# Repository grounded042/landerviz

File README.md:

# LanderViz

LanderViz is a stand-alone audio visualizer for a ZSA Moonlander Mark I. A
SparkFun Pro Micro RP2040 sits between the keyboard and the Mac, analyzes a
stereo audio pair, and targets 30 frames per second of per-key color to custom
Moonlander firmware. No visualizer program runs on the Mac during stand-alone
operation; the optional Mac preview exists only for development.

The complete stereo prototype has been hardware validated: both audio channels
drive the display and keyboard independently, the Moonlander receives RGB
frames, and ordinary typing passes through to macOS. The Moonlander output is
specifically for **revision A**.

## Architecture

```text
                             ordinary keyboard/mouse/media reports
Moonlander -- downstream USB --> Pro Micro RP2040 -- upstream USB --> hub --> Mac
     ^                           |  host toward keyboard; device toward Mac
     |                           +-- stereo ADC + FFT
     +---------- RGB frames -----+-- LCD + rotary encoder
```

- **HID** (Human Interface Device) is the standard USB keyboard/mouse protocol.
  TinyUSB makes LanderViz appear as a composite keyboard, mouse, media-key, and
  system-control device to the Mac and forwards the Moonlander's reports.
- **PIO** (Programmable Input/Output) is configurable digital hardware inside
  the RP2040. Pico-PIO-USB uses it to create the second USB connection on GPIO0
  and GPIO1, where LanderViz acts as the host for the real Moonlander.
- **Raw HID** is a vendor-defined HID data pipe. LanderViz owns that pipe and
  sends each RGB frame as eight 32-byte packets. The Moonlander publishes only
  complete frames, so a dropped packet cannot make a torn frame.
- **ADC** (analog-to-digital converter) samples biased left and right audio on
  GPIO26 and GPIO27. The RP2040 uses ARM CMSIS-DSP's 256-point Q15 **FFT**
  (fast Fourier transform) to split audio into frequency bands. FLOW averages
  left and right before one FFT; SPECTRUM retains one FFT per channel. Q15 is a
  signed fixed-point number format with 15 fractional bits.

The custom firmware deliberately removes ZSA's Oryx Raw HID module. Normal
typing, layers, macros, mouse keys, media keys, and N-key rollover remain; the
live Keymapp layout display and Oryx Live Training do not. Keymapp is not
required for normal use and remains optional as a firmware flashing tool.

If RGB packets stop for 500 ms, the keyboard returns to the layer lighting from
your Oryx layout. Both firmwares cap LED brightness at 175/255.

## Reproducible Nix builds

The flake pins the Raspberry Pi Pico software development kit, TinyUSB,
Pico-PIO-USB, ARM CMSIS-DSP, ZSA QMK Firmware 25, and QMK's required
submodules.
The generated Oryx keymap source is vendored as reviewable text under
`moonlander/oryx`; its source and refresh procedure are documented in
`moonlander/README.md`.

```sh
nix flake check
nix build .#rp2040 -o result-rp2040
nix build .#moonlander -o result-moonlander
nix build .#preview -o result-preview
nix build .#power-capture -o result-power-capture
nix build .#rp2040-power-test -o result-rp2040-power-test
nix build .#rp2040-encoder-test -o result-rp2040-encoder-test
nix build .#moonlander-power-test -o result-moonlander-power-test
```

Artifacts:

- `result-rp2040/landerviz.uf2` — Pro Micro RP2040 firmware
- `result-moonlander/zsa_moonlander_reva_landerviz.bin` — Moonlander revision-A
  firmware based on Oryx layout `z9wlG`, revision `ARDpK`
- `result-preview/bin/landerviz-preview` — development-only Mac visualizer
- `result-power-capture/bin/landerviz-power-capture` — FNIRSI FNB58 power
  measurement logger
- `result-rp2040-power-test/landerviz.uf2` — manual all-white power-test
  controller firmware
- `result-rp2040-encoder-test/landerviz.uf2` — rotary encoder wiring and
  transition diagnostic
- `result-moonlander-power-test/zsa_moonlander_reva_landerviz.bin` — matching
  Moonlander revision-A diagnostic firmware with its receive cap raised to 255

`nix develop` provides the pinned build tools for manual CMake work. The actual
build board name is `sparkfun_promicro`; the flake already supplies it.

### USB power capture

The development-only power logger reads an FNIRSI FNB58 through its separate
micro-USB `PC` port while the meter remains inline between the powered hub and
LanderViz. **HID** (Human Interface Device) is used here only as the meter's
driver-free USB data transport. The tool reports the lowest measured USB bus
voltage and the average and highest current and power. It can also retain every
sample as a **CSV** (comma-separated values) file for later inspection.

```sh
nix run .#power-capture -- --duration 30
nix run .#power-capture -- --duration 30 --csv /tmp/landerviz-power.csv
```

Leave the FNB58 `PD` communication switch off. The logger implements only the
meter's initialization and measurement-poll commands; it has no fast-charge or
voltage-trigger feature. Its USB measurement protocol is based on the
independently documented [OpenFNB58 protocol](https://github.com/yeckel/OpenFNB58).

#### Controlled maximum-light test

The power-test artifacts are measurement tools, not production firmware. Flash
the diagnostic Moonlander image first, then the diagnostic RP2040 image. The
keyboard starts black after the USB bridge connects. A short press on the
encoder knob advances all keys through white levels 0, 64, 128, 175,
200, 225, and 255; a press held longer than 800 milliseconds moves down one
level. The LCD always shows the commanded level. A controller reset returns to
black.

Run the FNB58 logger during the test and advance only after checking the prior
plateau. Stop if USB disconnects, the keyboard resets or flickers, or its supply
voltage becomes marginal. Restore the ordinary `moonlander` and `rp2040`
artifacts after measurement; they retain the production cap of 175.

The 2026-10-22 breadboard test validated 175 as the production limit. With the
revision-A serial LCD configuration, a five-minute all-white soak at 175
averaged 0.713 A and peaked at 0.724 A; the lowest upstream VBUS reading was
5.174 V. White at 200 had previously shifted red/orange and recovered only
after reducing the test level to 64; 225 and 255 also failed. This is evidence
of a sustained-load limit somewhere in the prototype's downstream power path
even though voltage at the upstream FNB58 remained stable. Do not raise
`BRIGHTNESS_CAP` above 175 on the breadboard. [PCB.md](PCB.md) records the
complete measurement baseline and the remaining USB-C power decision.

### Mac visualization preview

The development-only preview uses the same C++ audio analyzer, FLOW v3
components, and Moonlander LED mapping as the RP2040 firmware. It defaults to
the accepted FLOW v3 compositor; press `T` to cycle through v1, the frozen v2
baseline, and v3 at the same playback position. The comparison engines and
isolated labs remain preview-only.
See [FLOW v3 design contract](FLOW_V3_DESIGN.md) for the model and acceptance
criteria. FFmpeg decodes MP3, M4A, WAV, FLAC, and other common audio files;
SDL2 provides playback and draws all 72 simulated keys. Neither dependency is
included in the firmware.

```sh
nix run .#preview -- ~/Music/test-track.mp3
nix run .#preview -- --demo
nix run .#preview -- --demo-kicks
nix run .#preview -- --fps 25 ~/Music/test-track.mp3
nix run .#preview -- --travel-ms 110 ~/Music/test-track.mp3
nix run .#preview -- --trace /tmp/flow.csv ~/Music/test-track.mp3
nix run .#preview -- --analyze-only --trace /tmp/flow.csv ~/Music/test-track.mp3
```

The macOS package also includes a real application bundle. Opening it with no
arguments starts the demo; use `--args` to play a local audio file:

```sh
open -n result-preview/LanderViz.app
open -n result-preview/LanderViz.app --args --fps 30 "/absolute/path/song.mp3"
```

Use `T` to cycle FLOW v1/v2/v3 at the same playback position, left/right or
number keys 1–5 to change mode, space to pause, `R` to restart, `G` to compare
realistic light spill with the flat diagnostic view, `M` to cycle the v3
Combined/Energy/Attack/Texture/Mid/Bass views, `B` to compare Bass A/B inside
the Bass Lab, `E` to compare Combined with/without its capped Energy floor, `A` to
compare Combined with/without its accepted Attack shaping, `X` to compare
Combined with/without its bounded Texture hue influence, `[`/`]` to change the
simulated frame rate, comma/period to make FLOW
slower/faster in 10 ms increments, and escape or `Q` to quit. The title bar
shows the active FLOW engine, mode, frame rate, FLOW travel time, and lighting
style.
`--travel-ms N` sets the initial 50–1000 ms per-column travel time. `--frames
N` exits after N rendered frames and is intended for automated smoke tests.
`--flow-v1`, `--flow-v2`, or `--flow-v3` selects an engine at startup. The
default is v3. Within v3, `M` cycles the Combined, isolated Energy, isolated
Attack, isolated Texture, isolated Mid, and frozen Bass views;
`--combined-lab`, `--energy-lab`, `--attack-lab`, `--texture-lab`, `--mid-lab`,
and `--bass-lab` choose the startup view, with Combined as the default. In the
Bass Lab, `B` switches between the frozen direct bass envelope (Lab A) and
bounded slow-bed contrast expansion (Lab B); `--bass-a` and `--bass-b` choose
the bass version, with the accepted Lab B bass foundation as the default.
Combined always uses Bass B. Its Energy floor is enabled by default;
`--energy-floor` and `--no-energy-floor` select it at startup.
Combined's Attack shaping is also enabled by default; `--attack-shape` and
`--no-attack-shape` select it at startup. Attack shaping requires the Energy
floor integration, so disabling the floor displays the earlier no-floor
Combined baseline. Texture integration is enabled by default;
`--texture-surface` and `--no-texture-surface` select it at startup. It is
layered on the accepted Energy and Attack integration, so disabling either
shows that earlier baseline. `--trace
FILE.csv` records the pre-gain gate,
shared gain, per-channel energy, centroid, dominance, and low/mid/high onset
flux, adaptive thresholds, strengths, and trigger decisions once per analyzed
audio frame, plus the v3 bass and midrange level, absolute and contrast
centroids, contrast strength, base/target/rendered hue, and presence
diagnostics, the isolated Energy Lab raw, target, and smoothed levels, and
Attack Lab's raw and normalized positive-rise signals. Texture Lab adds its raw
high-frequency share, target, smoothed texture, and presence. Add
`--analyze-only` to process the complete track without opening a window or
playing audio; it requires `--trace` and an audio file and prints the three
accepted v2 onset counts when complete. FLOW v2 keeps its base color and
energy stereo, but merges per-band energy across channels for shared rhythmic
events so a panned hit launches one wavefront across both keyboard halves.
`--demo-kicks` plays an isolated 120 BPM kick train and reports detected versus
generated v1 kicks in the title bar. V1 kick packets are enabled only in that
diagnostic mode while the detector is being calibrated. V3 Attack Lab is a
separate continuous positive-rise diagnostic with no threshold, refractory
timer, or binary beat trigger. Accepted Combined uses that signal only to
tighten an existing ribbon edge; it cannot independently create light.

Before flashing a Moonlander build, confirm the keyboard's hardware revision.
ZSA's command-line flasher can accept the local file:

```sh
nix run github:zsa/zapp -- flash result-moonlander/zsa_moonlander_reva_landerviz.bin
```

That command intentionally is not run by the build. Hold BOOT while connecting
the Pro Micro, then copy `landerviz.uf2` to the `RPI-RP2` drive to flash it.

## Minimal prototype parts

In addition to the parts already listed, the USB bridge needs:

- one USB-A female breakout, or a known-good female extension cable cut open;
- two 22 ohm resistors, one in each USB data wire;
- one bulk electrolytic capacitor, start with 470 microfarads rated for at
  least 6.3 V;
- a way to make reliable connections to the headerless boards: normally two
  12-pin 0.1-inch male headers for the Pro Micro, soldered in place;
- one 3.5 mm TRS stereo jack breakout and a male-to-male TRS cable, four
  100 kilohm resistors, and two 10 microfarad coupling capacitors;
- one 5 V, HD44780-compatible 16x2 LCD with a soldered PCF8574T I2C backpack;
  and
- one four-channel, bidirectional 3.3 V-to-5 V logic-level converter.

No larger controller or extra interface board is required. Keep the USB data
wires short; a solderless breadboard may be electrically marginal at USB full
speed, so first failures there do not automatically imply a firmware bug.

## Wiring

### USB bridge

The Pro Micro's onboard USB-C connector is the upstream/device connection to a
**data port** on the powered Anker hub. Never use a PowerIQ charging-only port.
The added USB-A female connector is the downstream/host connection for the
Moonlander. Use a known-good data cable: a charging-only USB cable can power the
Moonlander's startup LEDs while leaving LanderViz at `WAIT` indefinitely.

| USB-A female contact | Pro Micro connection |
|---|---|
| VBUS | backside `V` USB-power pad |
| D- | GPIO1 through 22 ohms |
| D+ | GPIO0 through 22 ohms |
| GND | GND |

**VBUS** (USB bus voltage) is the nominal 5 V supply. Use the backside `V` pad,
which is connected directly to USB-C VBUS. Do not power the Moonlander from the
`+` pin: that path is downstream of the board's 500 mA resettable fuse and
Schottky diode, so the RP2040, display, and Moonlander would share the fuse and
the Moonlander would receive about 4.8 V. Put the 470 microfarad bulk capacitor
between the USB-A VCC row and GND near the connector: capacitor positive to
VCC, negative stripe to GND. The firmware requests 500 mA from the upstream USB
hub and caps keyboard brightness to reduce LED current spikes. The final
serial-LCD breadboard test nevertheless peaked at 0.724 A under the diagnostic
all-white load, so the 500 mA declaration does not close the future PCB's
upstream power contract. The prototype held about 4.99 V at the downstream
connector during bring-up, but that measurement is not a guarantee for other
hubs or wiring. Do not connect the Moonlander to another power source at the
same time, and do not add capacitors to D+ or D-.

### PCF8574 serial liquid-crystal display

The revision-A prototype uses a PCF8574T backpack rather than the retired
six-wire parallel LCD connection. **I2C** (Inter-Integrated Circuit) is the
two-wire serial bus: SDA carries data and SCL carries the clock. **GPIO** means
general-purpose input/output pin.

The RP2040 pins are not tolerant of 5 V logic. Put a bidirectional logic-level
converter between the 3.3 V RP2040 bus and the 5 V backpack:

| Connection | Low-voltage side | High-voltage side |
|---|---|---|
| Converter power | `LV` to Pro Micro `3V3` | `HV` to the 5 V rail |
| Ground | `LV GND` to digital GND | `HV GND` to the same digital GND |
| SDA | GPIO2 to `LV1` | `HV1` to LCD `SDA` |
| SCL | GPIO3 to `LV2` | `HV2` to LCD `SCL` |
| LCD power | — | LCD `VCC` to 5 V; LCD `GND` to digital GND |

Leave converter channels 3 and 4 unused. Use the digital ground rail shared
with the USB breakout rather than adding the display return beside the analog
TRS return. The backpack supplies its own contrast trimmer and backlight
circuit, so the old external 10 kilohm trimmer and 100 ohm resistor are not
used.

The tested Teyleten Robot module responds at address `0x27` with the common
backpack mapping P0=RS, P2=enable, P3=backlight, and P4 through P7=D4 through
D7. Firmware also probes `0x3F`, runs the bus at 100 kHz, and updates only LCD
cells whose contents changed. This retained approximately 30 completed RGB
frames per second with no continuously missed audio buffers during FLOW.

In `FLOW` and `SPECTRUM`, row 0 shows a mirrored stereo frequency spectrum:
bass is at the outside edges and treble meets at the center. In the other
modes, row 0 shows independent left and right VU bars (volume-unit-style level
meters), peak hold, and `!` on clipping. Row 1 shows the mode and completed USB
RGB frames per second. It counts only full eight-packet frames delivered to the
Moonlander, rather than visualizer loop calls.

### Rotary encoder and menu

The validated EC11 rotary encoder uses GPIO4 for A, GPIO5 for B, and GPIO8 for
the push switch. Connect the middle pin on its three-pin side (the encoder
common) to digital GND. Connect either push-switch pin to GPIO8 and the other
to digital GND. All three inputs use the RP2040's internal pull-up resistors;
do not connect the encoder to 3.3 V or 5 V.

Clockwise rotation selects the next visualization and counterclockwise selects
the previous one. A short press cycles three vivid color schemes remembered
separately for each visualization until reboot. A press held longer than 800
ms opens the menu. Turn to select `DIAGNOSTICS`, `CALIBRATE INPUT`, or `EXIT`;
short-press to select. In diagnostics, turning selects the audio, gain, FLOW,
performance, and USB pages. Short-press returns to the menu and long-press
returns directly home.

The `rp2040-encoder-test` artifact shows raw A/B states, push-switch state,
position, direction, and rejected transitions. The installed encoder was
validated at exactly one count per detent in either direction with zero
rejected transitions.

### Mixer stereo audio to ADC0 and ADC1

Line audio swings above and below 0 V, while the RP2040 ADC accepts only 0 to
3.3 V. Each channel gets its own two-resistor divider that biases its ADC node
to 1.65 V. Its coupling capacitor blocks direct current from the mixer. The
channels must not share a bias node, because that would mix them together.

```text
                         3.3 V                            3.3 V
                           |                                |
                         100k                             100k
                           |                                |
TRS tip/left --- 10 uF ----+--- GPIO26   TRS ring/right -- 10 uF --+--- GPIO27
                           |                                      |
                         100k                             100k
                           |                                |
TRS sleeve ----------------+------------- GND --------------+
```

For a polarized electrolytic coupling capacitor, put its positive lead toward
the 1.65 V ADC node and its negative lead toward the mixer jack. A non-polarized
capacitor works either way. Start with the mixer's output level low and raise it
until the display is useful without showing `!`.

The passive mixer used by the prototype attenuates its output, so firmware
applies a fixed `8.0x` (`+18 dB`) visualization gain before the FFT. Adjust
`AUDIO_INPUT_GAIN` in `main.cpp` if the source level changes. The LCD `!`
indicator still reports clipping at the physical ADC input, before this gain.
Analysis removes each sample frame's measured DC bias before calculating its
level, so normal tolerance around the nominal 1.65 V bias does not appear as
audio on the meters. Keyboard effects use a sensitive `-48 dBFS` logarithmic
curve. LCD metering and silence detection add a `-30` to `-24 dBFS` soft noise
gate, keeping the meter empty at the prototype's measured noise floor without
reducing normal keyboard animation. Silence detection also requires three of
four consecutive analysis frames to clear that gate, so isolated noise spikes
do not prevent the aurora from starting. `dBFS` means decibels relative to the
ADC's full-scale input.

For the numbered five-pin stereo breakout selected for this prototype, the
reported mapping is pin 1 ground/sleeve, pin 2 right/ring, pins 3 and 4 jack
detection switches, and pin 5 left/tip. Confirm that mapping with continuity
mode before applying power, because generic breakout batches can change. Leave
pins 3 and 4 disconnected.

### Ground routing and noise checks

The prototype uses two breadboard ground rails to keep noisy USB, keyboard,
and LCD return current out of the sensitive audio wiring:

- The audio rail connects the TRS sleeve, the bottom 100 kilohm resistor of
  each bias divider, and one Pro Micro GND pin.
- The digital rail connects USB-A GND, bulk-capacitor negative, the LCD and
  level-converter grounds, the encoder common and push switch, and the other
  Pro Micro GND pin.

Both Pro Micro GND pins are internally the same electrical node. This is
`star-ground` routing: the two current paths meet at the controller instead of
sharing a long breadboard rail. It does not electrically isolate the audio and
USB systems.

Solderless breadboard power rails are often split in the middle. With all power
removed, use the meter's continuity or lowest resistance range to verify every
ground point. First touch the probes together to learn their own resistance;
each ground-to-GND reading should be close to that value, and no ground rail
should read open. Never measure resistance on a powered circuit.

During bring-up, an audible high-pitched whine appeared only with the TRS cable
connected and cleared after unplugging and reconnecting the mixer's USB-C
power. If it returns, treat mixer power and the audio/USB ground path as the
first suspects. A short shielded cable can reduce radiated pickup, while a
stereo transformer ground-loop isolator can break a persistent shared-ground
loop; ordinary "directional" analog cables cannot provide that isolation.

## Firmware behavior

See [Visualization design principles](docs/visualization-design.md) for the
shared motion, smoothing, sampling, and validation rules used by every mode.

The five selectable modes are:

- `FLOW` (default): the accepted v3 compositor turns each analyzed audio frame
  into one timestamped music slice. FLOW averages the stereo waveform to mono
  before analysis so its single cohesive ribbon has more CPU time; independent
  left/right RMS loudness is still retained for metering and silence detection.
  Bass supplies a continuous body, midrange content selects its vivid hue,
  whole-spectrum energy supplies a capped visibility floor, positive spectral
  change sharpens its existing leading edge, and sustained high-frequency
  content adds a bounded hue shift. These properties travel together as one
  ribbon rather than independent rows or flashes. Adjacent slices and
  fractional physical key coordinates are interpolated as the ribbon moves
  outward at roughly 110 ms per column;
- `SPECTRUM`: left audio drives the left keyboard half and right audio drives
  the right half; each half has bass at the outside and treble at the center,
  utility keys mirror the adjacent treble column, and thumbs pulse with bass;
- `PULSE`: whole-board kick pulse with a slowly rotating hue;
- `VU`: independent left/right meters that fill each keyboard half from green
  at the bottom to red at the top, with partial-row brightness and smoothed
  attack/release;
- `IDLE`: slowly drifting blue, teal, green, and violet aurora, also used after
  five seconds of quiet.

The RP2040 targets 30 complete keyboard frames and 10 LCD refreshes per second.
It retains 256 audio samples per FFT for frequency resolution, but analyzes
every other captured window—about 30.5 analysis frames per second—to leave the
USB and LED renderer more CPU time. Decimation happens when capture windows
complete, so intentionally skipped windows never occupy the consumer buffer or
inflate the missed-window counter. FLOW services upstream USB after its mono
FFT; stereo modes also service it between channels. The FLOW renderer services
USB between small coordinate batches. These yields do not change the analyzed
values or rendered key colors. Time-domain mono can cancel rare material whose
left and right channels have opposite phase; that is an accepted trade-off for
the measured CPU headroom.
The Moonlander's LED-driver flush interval is 26 ms (a ceiling of about 38
frames per second), so 30 Hz leaves timing margin while exceeding the roughly
27 Hz motion target.

FLOW's vivid OKLCH colors (a perceptual lightness/chroma/hue color model) use a
generated, interpolated **LUT** (lookup table) stored in flash. This preserves
the preview palette without running trigonometry and gamut searches for every
key on the RP2040. Regenerate it with:

```sh
python3 tools/generate_flow_v3_color_lut.py src/flow_v3_color_lut.inc
```

While FLOW is selected, LCD row 1 rotates every two seconds among the normal
mode/frame-rate page and three steady-state maximum profiling pages. The
counters reset once, one second after USB enumeration completes, so startup
does not permanently contaminate them. Times are shown in tenths of a
millisecond and cap at `999`: `A` is total audio analysis time, `F` is its
FFT/band-analysis portion, `E` is v3 feature extraction, `R` is render/submit
time, `M` is genuinely missed due analysis windows, `D` is the upstream USB
device-service gap, `H` is the downstream USB host-service gap, and `K` is
keyboard-report forwarding latency. These counters exist to validate the
firmware on the real RP2040; desktop preview timing is not a substitute.

FLOW keeps the fixed 8x (+18 dB) passive-mixer compensation. After the FFT, it
subtracts calibrated noise power per frequency band and applies a shared
adaptive gain before any FLOW feature extraction. Gain scaling commutes with
the linear FFT; placing it here allows spectral noise removal first. The
adaptive stage targets a useful program level, reduces gain over sustained
loud passages, recovers slowly for quiet tracks, and cannot increase gain
while the noise-relative gate is closed. A single beat therefore remains part
of the music rather than being immediately normalized away.

After calibration, the music gate also accepts sustained energy in at least
two overlapping mel-frequency bands above their individual noise floors. This
keeps genuinely quiet passages alive even when their total RMS level is near
the broadband floor. Opening still requires three consecutive analysis frames,
and a half-second close hold bridges gaps between notes without leaving paused
audio visibly active.

To calibrate the current input hardware, pause audio and select
`CALIBRATE INPUT` from the encoder menu. Holding the encoder button throughout
the 1.2-second boot splash remains a startup shortcut. `SILENCE` counts through
a three-second measurement while USB service continues. `CALIBRATION OK`
reports the accepted broadband floor. `CALIBRATION BAD` means the input varied
too much and should be retried with audio paused. Calibration is deliberately
RAM-only in this validation build and therefore does not survive a reboot.

The menu's five diagnostic pages expose:

- Audio: largest pre-gain RMS and peak levels in the latest one-second window,
  in decibels relative to full scale (dBFS).
- Gain: adaptive gain, calibrated physical-input noise floor, and whether its
  gate is open (`O`) or closed (`C`).
- FLOW: one-second maximum raw bass and rendered body on a 0–999 scale, plus
  missed analysis windows.
- Performance: completed RGB frames per second plus maximum analysis and
  rendering time in tenths of a millisecond.
- USB: current host status plus maximum device-task, host-task, and keyboard
  forwarding intervals in tenths of a millisecond.

The input readings divide out `AUDIO_INPUT_GAIN`, so they describe the voltage
that actually reached the ADC rather than either visualization gain. Wait at
least two seconds after changing volume, then record the typical readings over
the same repeatable passage.

## Safe bring-up order

1. Verify that the physical Moonlander is revision A. Do not infer this only
   from the downloaded filename.
2. Flash the custom Moonlander firmware while it is connected directly to the
   Mac. Test every layer plus ordinary, mouse, media, and system keys. The
   visualizer receiver will simply time out to normal layer colors.
3. Flash the RP2040 and power it from the hub with no downstream keyboard or
   breadboard circuit attached.
4. Remove power, mount the headers and breadboard wiring, then check the 5 V,
   3.3 V, ground, and USB wiring for shorts.
5. With the Moonlander disconnected, test the encoder and LCD separately.
6. Add the stereo audio inputs and begin with the mixer output level down.
7. Check the USB data and power wiring once more, connect the Moonlander last,
   and validate typing before enabling visualization frames.

Keep the unmodified Oryx `.bin` from the original download outside this
repository so reverting the keyboard is straightforward.

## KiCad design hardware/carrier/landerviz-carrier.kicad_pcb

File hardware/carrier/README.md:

# PGA2350 carrier — Rev A

2026-11-07. Open **`landerviz-carrier.kicad_pro`** in KiCad, then open its
schematic or PCB Editor. This is a separate project from the preserved bare-chip design.

**Carrier Rev A bare boards are ordered from OSH Park.** The reviewed
90 × 75 mm two-layer hardware is frozen. See [ORDER_STATUS.md](ORDER_STATUS.md)
and [SHOPPING.md](SHOPPING.md) for the next component purchases. Full assembly,
firmware port and functional bring-up remain work for the arriving boards.
Current revision markings and four dedicated M3 mounting holes are described in
[MECHANICAL.md](MECHANICAL.md). The separate [Astra handoff](ASTRA_REVIEW_BRIEF.md)
identifies the original frozen review package. The completed review and
current corrections are tracked in [REVIEW_RESOLUTION.md](REVIEW_RESOLUTION.md).
See [ROUTING.md](ROUTING.md), [PLACEMENT.md](PLACEMENT.md) and
[the routed overview](routing-overview.svg).
The [manufacturing release](releases/rev-a/README.md) preserves the exact
ordered ZIP. The [bare-board quote guide](QUOTING.md) records its settings
and the US pricing comparison.
The [parts/fit checklist](PARTS.md) and [inventory CSV](parts.csv) separate owned
parts, missing-part candidates and header/socket contacts still to confirm.
The [assembly preparation guide](ASSEMBLY.md) records soldering order, polarity
and connector orientation for the current draft.
`prepare_fit_template.py` produces a one-page US Letter PDF at actual size
with a one-inch scale check, for comparing owned parts against the saved board.
Approved direction and accepted always-powered-output limitations are in
[../CARRIER.md](../CARRIER.md).

## Included circuits

- Assumed A4 PGA2350 module; native USB goes to the input connector and
  GPIO0/1 provide the keyboard USB host through 22 ohm resistors.
- Two Soldered **333011** USB-C breakout modules. Both arrive with the tiny
  connector soldered; the user solders ordinary header pins. Input CC1/CC2
  each have their own 5.1k pull-down. Output CC1/CC2 each have their own 22k
  pull-up to 5 V, advertising 1.5 A as in the original downstream design.
  This is not proof of upstream entitlement or continuous system capability;
  supported use remains the measured Anker data port and brightness cap.
- Direct shared 5 V supply to keyboard, LCD and module VB, with 470 µF bulk
  capacitance. No input-ramp chip, attach-controlled power switch, local
  electronic current limiter or reverse blocking. The bulk capacitor charges
  directly at plug-in, as on the prototype. Previously discussed limitations
  were accepted for this prototype; do not silently add back those circuits.
- Separate left/right 22k/22k bias dividers, 10 µF coupling, 10k series and
  2.2 nF shunt filters. ADC0/1 move to GP40/41 on RP2350B.
- Direct-mounted Same Sky **SJ1-3533NG** right-angle TRS audio jack, with
  three downward-facing solder terminals. It replaces the old five-pin breakout.
- Four through-hole Vishay **BAT85S-TR** Schottky diodes replace the two tiny
  BAT54S dual-diode packages in the earlier PCB candidate. This retains the
  rail-clamp topology with solderable individual parts. Cathode pin 1 has the
  black band. Leakage/input-overdrive behaviour is not established by the
  earlier small-signal simulation; do not claim a guaranteed safe audio range.
- Existing BSS138 four-channel level converter, using channels 1/2 for the
  serial LCD; encoder A/B/push on GP4/5/8 and accessible boot/reset switches.
- Green 3 mm status LED D5 on GP6 through R13 (1k). GPIO high lights it;
  firmware-driven status behaviour will be implemented in the PGA2350 port.

There are **32 schematic assembly positions**: 13 resistors, 5 capacitors,
4 clamp diodes, 1 status LED, 4 connector/module positions J1–J4, 3 switches/encoder positions,
and 2 modules U1/U2. Headers and sockets add solder joints and must be included
in the physical bill of materials, not treated as free or already installed.
No optional expansion connectors or new visualizer features are included.

## Verified sources and boundaries

[PGA2350 schematic](https://cdn.shopify.com/s/files/1/0174/1800/files/Pimoroni_PGA2350_Schematic.pdf?v=1724926880)
and [pinout](https://cdn.shopify.com/s/files/1/0174/1800/files/pga2350_pinout_diagram.pdf?v=1723124465)
establish native USB access, module supplies and RP2350B ADC assignments.
The module includes native USB series resistors; no duplicate pair is added.
Carrier module pad identifiers are signal names (GP0, VB, etc.), not an
unverified numeric connector mapping. The study's physical footprint maps
them to the manufacturer's grid. The user accepts that drawing and the earlier
paper fit for ordering; full socket/module mating remains an assembly step.

Soldered 333011 was checked by exporting the manufacturer's actual v1.2.0
KiCad schematic to a netlist. Its eight-pin header is:

| Pin | Signal |
|---|---|
| 1 | GND |
| 2 | CC2 |
| 3 | SBU2 (unused) |
| 4 | D− |
| 5 | D+ |
| 6 | SBU1 (unused) |
| 7 | CC1 |
| 8 | VBUS / 5 V |

The manufacturer netlist connects A6/B6 together for D+, A7/B7 for D−,
all four VBUS contacts together, and all grounds/shield together. It contains
no termination resistors; the carrier therefore supplies both port roles
without removing small parts from the modules.

Manufacturer source:
[333011 product](https://soldered.com/products/usb-c-female-connector-breakout),
[hardware repository](https://github.com/SolderedElectronics/USB-C-female-connector-breakout-hardware-design),
[examined v1.2.0 schematic](https://github.com/SolderedElectronics/USB-C-female-connector-breakout-hardware-design/blob/main/CAD/V1.2.0/USB-C%20female%20connector%20breakout.kicad_sch).
Downloaded source SHA-256:
`7099bd95e128ead42f08a6231950e0f57268cbae41e147238cb3c97377c63361`.
The examined module source is retained temporarily outside the repo; no
manufacturer board design was copied into our project. Confirm the delivered
module's revision/pin order during mechanical review.

Diode source: [Vishay BAT85S datasheet](https://www.vishay.com/docs/85513/bat85s.pdf),
DO-35 axial case, black cathode band. Ordinary resistors/capacitors can be
sourced from known inventory if values, tolerances, ratings and dimensions
match. Their package sizes remain pending; no generic kit part was assigned
an invented manufacturer number.

The new jack uses the manufacturer's pinout: **1 sleeve/ground, 2 tip/left,
3 ring/right**. KiCad names its corresponding pads S, T and R. Do not reuse the
old breakout's 1/2/5 numbering. The
[manufacturer family datasheet](https://www.sameskydevices.com/product/resource/sj1-353xng.pdf)
covers 3-, 4- and 5-contact variants; the selected **3533NG** omits pins 4/5.
Its drawing was visually checked against the installed circular-hole footprint.
No old audio-breakout measurements or mating header are needed for this choice.
The user confirmed the level converter's reversed row direction and capacitor
fit on November 7. The converter footprint now matches those labels. The
processor's published dimensions and earlier paper fit are accepted for ordering;
full socket/module mating remains an assembly step.
The selected encoder is now **Same Sky ACZ11BR1E-20FD1-12C**, with 12 detents
and a push switch. The manufacturer documents hand-soldering limits; see
[ENCODER.md](ENCODER.md) for sourcing, exact pin pattern and the deliberate
round shell-hole choice. The previous Bourns was superseded after Astra review.

## Validation

KiCad 10.0.6 electrical-rules check (ERC): **zero findings**, with no rule
waivers/exclusions added. The independent exported-netlist audit passes
**16 requirements**: port pin order and terminations, unused sideband pins,
power branches, host series paths, jack channels, both audio networks and
clamp/coupling polarity, isolated ADC nodes, display voltage sides, controls,
module grounds, separate bias nodes, and the LED's polarity/series resistor.

Twelve tests run against the actual exported netlist: one accepts the clean
export; eleven deliberately corrupt a copy in memory and verify detection of
reversed coupling capacitor, reversed clamp, shared bias, wrong source CC
termination, wrong ADC routing, 5 V connected into audio, reversed LED,
bypassed/wrong LED resistor, 5 V fed into its GPIO branch and swapped jack channels. These tests do
not edit the schematic or merely repeat a zero-error ERC report.

During drafting, the independent audit caught a rotation/pin-coordinate error
that ERC did not detect. It was corrected and both checks rerun before this
draft was reported. The audit is connectivity evidence, not physical or
functional validation. The saved placement adds pad/coordinate/courtyard
auditing and fourteen placement checks, including injected faults, described in PLACEMENT.md.
The routed board is checked separately from the saved, unrouted placement
baseline. See ROUTING.md for the copper checks and their limits.
Generated exports live in ignored
`../fabrication/carrier-draft-20261106/` (PDF, SVG, netlist, ERC and audit JSON).

## Cost and next work

Prices checked 2026-11-06, excluding shipping/tax:

| Item | Quantity | Unit price | Subtotal |
|---|---:|---:|---:|
| [PGA2350 at PiShop](https://www.pishop.us/product/pga2350/) | 1 | $11.95 | $11.95 |
| [333011 at DigiKey](https://www.digikey.com/en/products/detail/soldered-electronics/333011/21720502) | 2 | $2.20 | $4.40 |
| **Processor and USB modules only** | | | **$16.35** |

This replaces the earlier $19.85 mixed-breakout comparison. Remaining costs:
missing diodes/passives, headers/sockets, bare carrier boards and shipping/tax.
DigiKey listed 399 modules when checked; availability/checkout price can change.
Soldered's own 22 × 22 mm module dimension is a reference, not a chosen carrier
outline. The user subsequently authorized a larger placement study: 90 × 75 mm.
Its area-based US bare-board estimate and remaining costs are in PLACEMENT.md.

Next: source remaining components for the ordered boards. The independent
Astra follow-up is GO and the user has placed the OSH Park order. Full socket/module mating and the
PGA2350 firmware port remain assembly/bring-up work.
Consolidate missing small parts at DigiKey to avoid repeated shipping charges.
The user will ensure A4 before buying the PGA2350; DigiKey's
module listing currently has no stock, so a single-module source remains open.
A4 stock confirmation remains an assumption, not a
reason to stop the independent schematic work. Firmware port is separate and
has not been implemented or flashed.

## Reproduce

Opening this project does not execute Python. `capture.py` explicitly
reproduces the generated draft and library; it overwrites those generated files,
so review/save manual schematic edits before invoking it again.

From the repo root:

```sh
PYTHONDONTWRITEBYTECODE=1 python3 hardware/carrier/capture.py
/Applications/KiCad/KiCad.app/Contents/MacOS/kicad-cli sch erc \
  --format json --exit-code-violations \
  -o /tmp/landerviz-carrier-erc.json hardware/carrier/landerviz-carrier.kicad_sch
/Applications/KiCad/KiCad.app/Contents/MacOS/kicad-cli sch export netlist \
  --format kicadxml -o /tmp/landerviz-carrier.xml hardware/carrier/landerviz-carrier.kicad_sch
PYTHONDONTWRITEBYTECODE=1 python3 hardware/carrier/check_netlist.py /tmp/landerviz-carrier.xml
PYTHONDONTWRITEBYTECODE=1 python3 hardware/carrier/test_check_netlist.py /tmp/landerviz-carrier.xml
```

Tools use Python's standard library and installed KiCad only. Cached KiCad
Device/Switch/power symbols carry the upstream library's licence and schematic
exception; see [../KICAD_LIBRARY_LICENSE.md](../KICAD_LIBRARY_LICENSE.md).
Custom module interface symbols were authored here from verified signal names.
No packages installed, firmware flashed, external files uploaded or commits made.

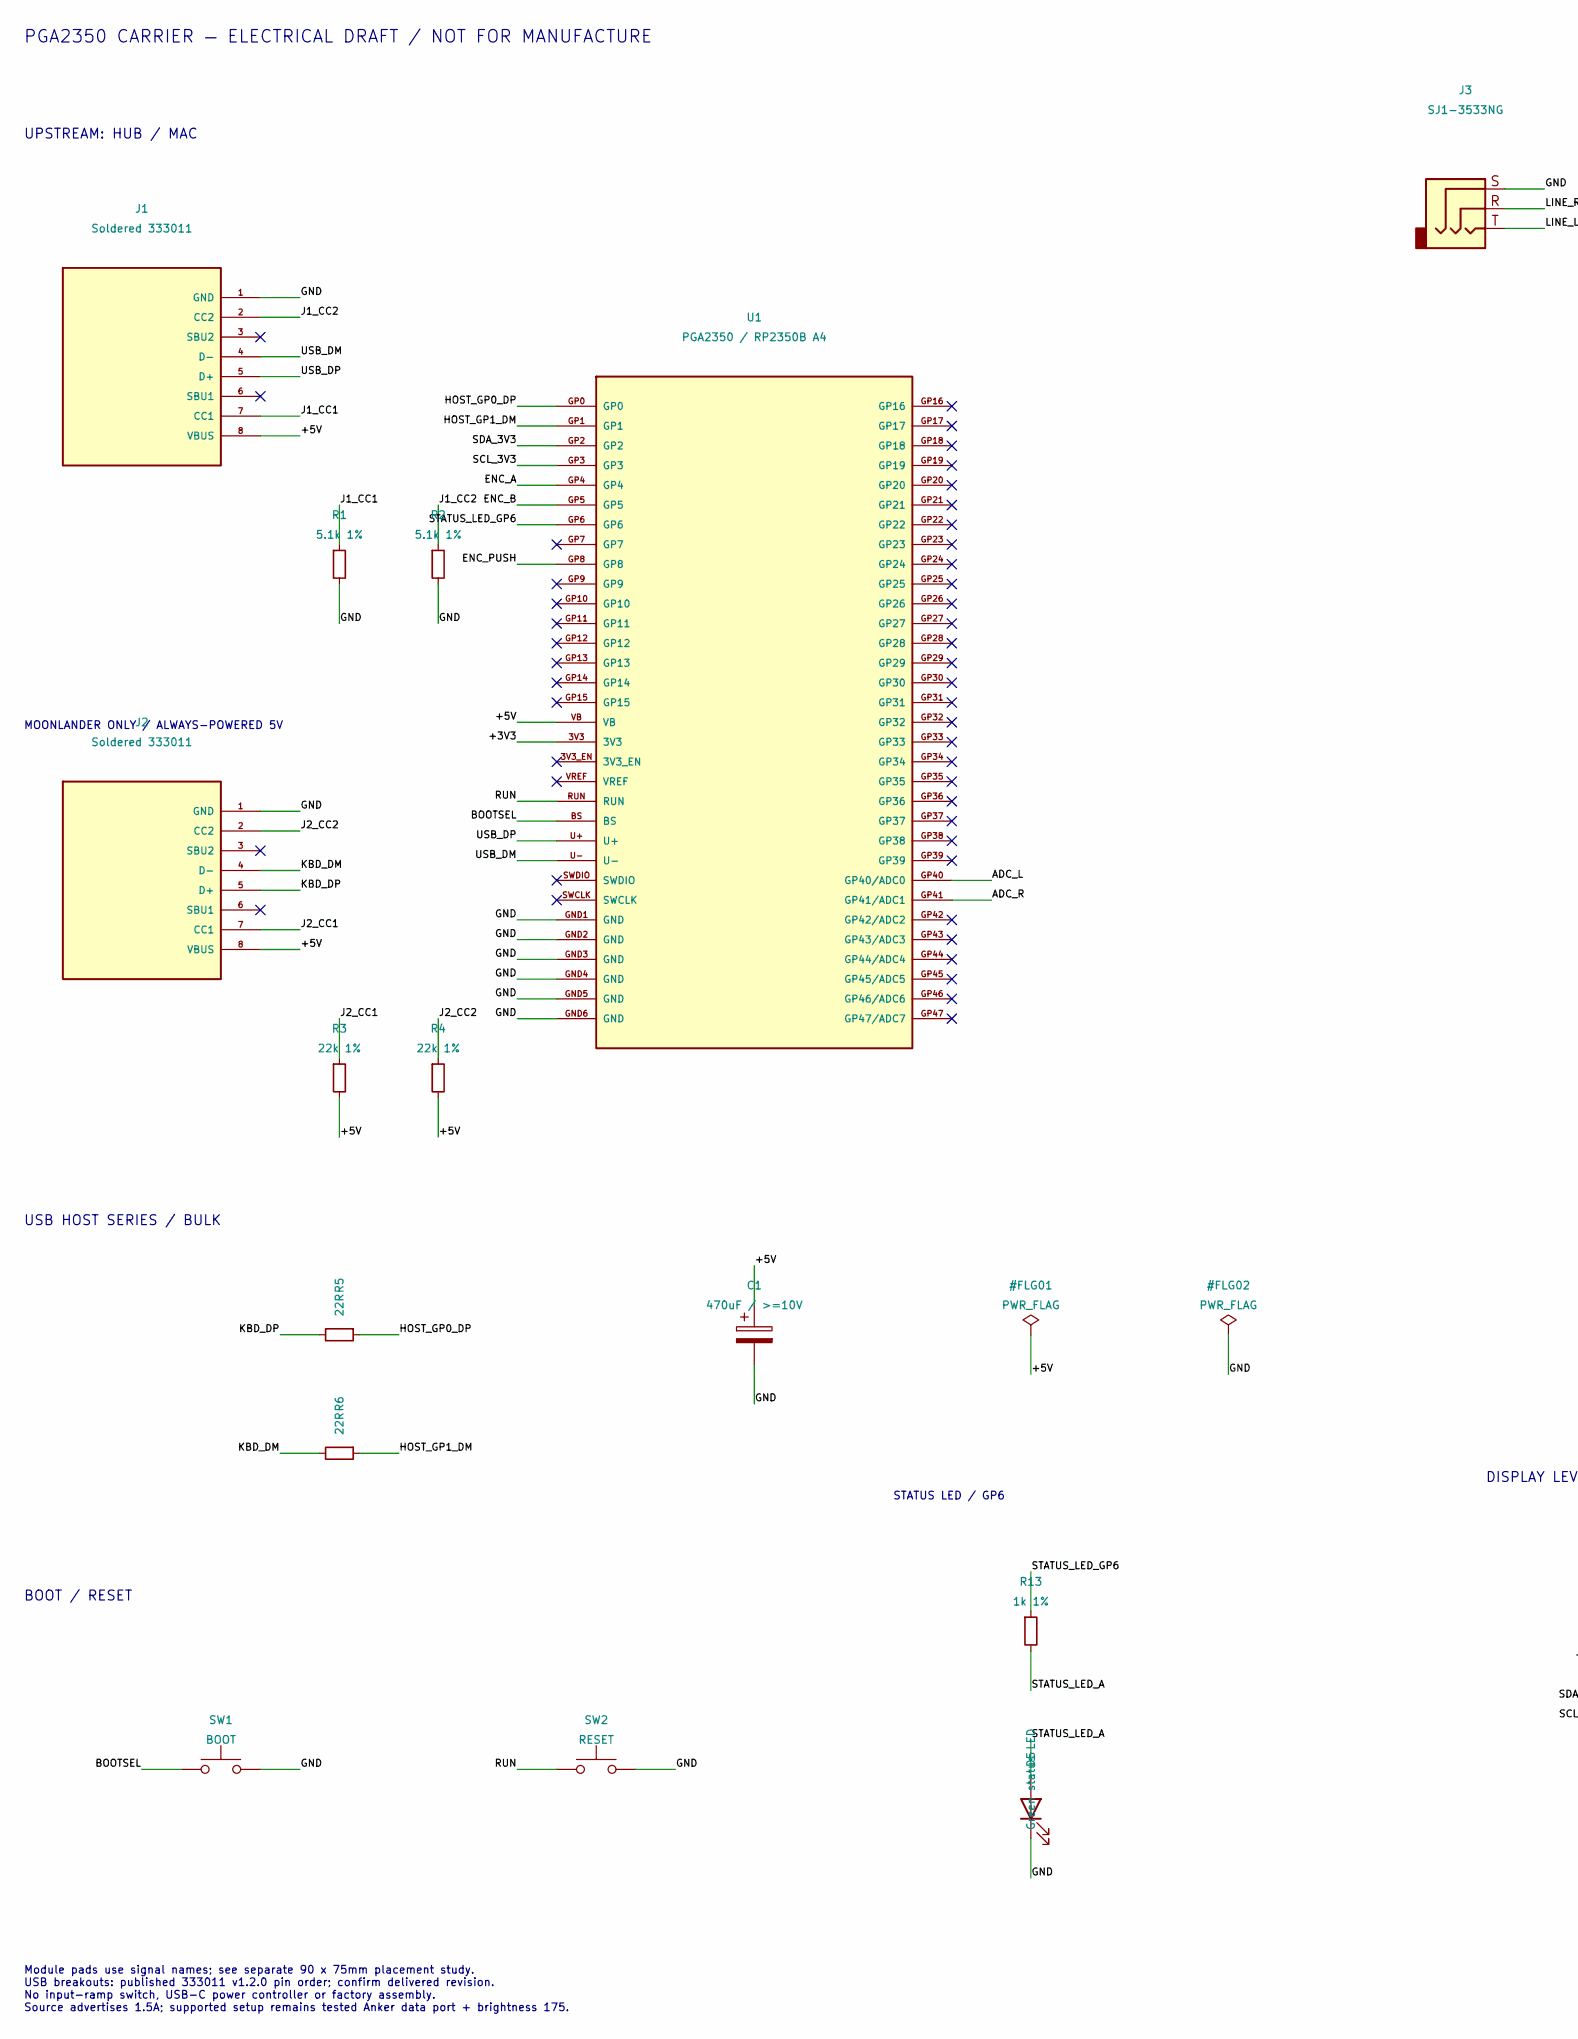
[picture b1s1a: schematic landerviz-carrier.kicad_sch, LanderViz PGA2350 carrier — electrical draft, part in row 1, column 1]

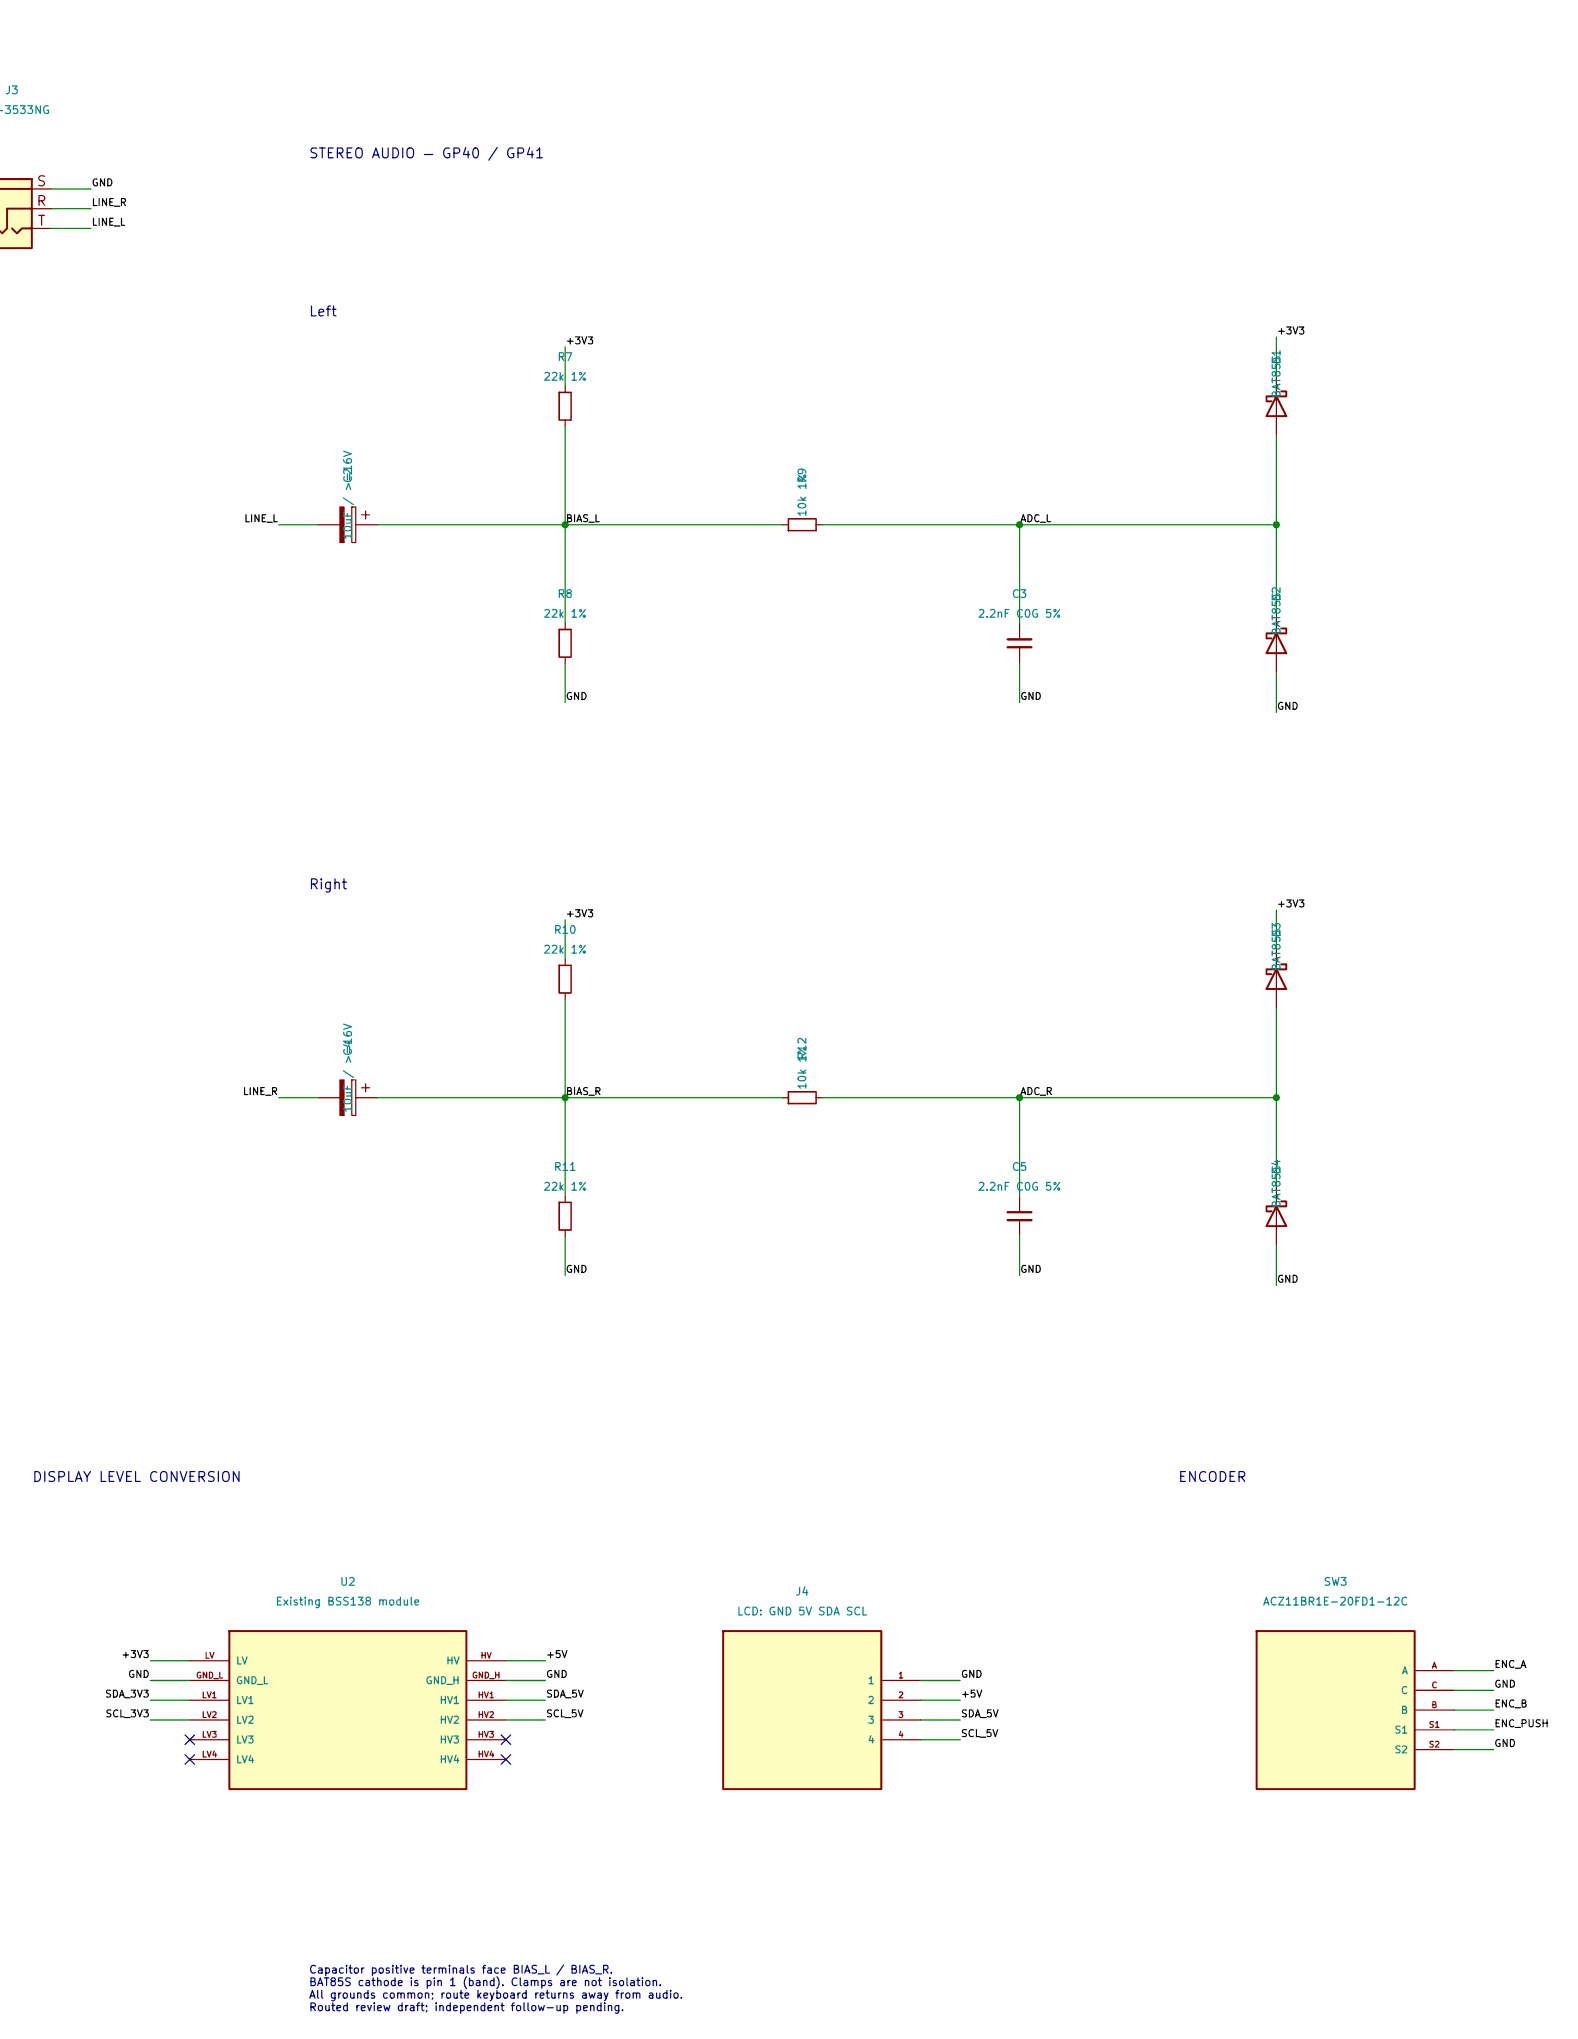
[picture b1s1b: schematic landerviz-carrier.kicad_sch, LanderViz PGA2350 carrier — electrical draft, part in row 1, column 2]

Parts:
C1: 470uF / >=10V; CP_Radial_D8.0mm_P3.50mm
C2, C4: 10uF / >=16V; CP_Radial_D6.3mm_P2.50mm
C3, C5: 2.2nF C0G 5%; C_Disc_D5.0mm_W2.5mm_P5.00mm
D1, D2, D3, D4: BAT85S; D_DO-35_SOD27_P7.62mm_Horizontal; MPN BAT85S-TR
D5: Green status LED; LED_D3.0mm; MPN WP710A10LZGCK
J1, J2: Soldered 333011; Soldered_333011; MPN 333011
J3: SJ1-3533NG; Jack_3.5mm_CUI_SJ1-3533NG_Horizontal_CircularHoles; MPN SJ1-3533NG
J4: LCD: GND 5V SDA SCL; PinHeader_1x04_P2.54mm_Vertical
R1, R2: 5.1k 1%; R_Axial_DIN0207_L6.3mm_D2.5mm_P7.62mm_Horizontal
R3, R4, R7, R8, R10, R11: 22k 1%; R_Axial_DIN0207_L6.3mm_D2.5mm_P7.62mm_Horizontal
R5, R6: 22R; R_Axial_DIN0207_L6.3mm_D2.5mm_P7.62mm_Horizontal
R9, R12: 10k 1%; R_Axial_DIN0207_L6.3mm_D2.5mm_P7.62mm_Horizontal
R13: 1k 1%; R_Axial_DIN0207_L6.3mm_D2.5mm_P7.62mm_Horizontal
SW1: BOOT; SW_PUSH_6mm
SW2: RESET; SW_PUSH_6mm
SW3: ACZ11BR1E-20FD1-12C; Encoder_SameSky_ACZ11BR1E_Vertical; MPN ACZ11BR1E-20FD1-12C
U1: PGA2350 / RP2350B A4; PGA2350_Socket_Grid; MPN PIM722
U2: Existing BSS138 module; Level_Converter_PROVISIONAL

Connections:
/+3V3: D1.1 (K), D3.1 (K), R7.1, R10.1, U1.3V3, U2.LV
/+5V: C1.1, J1.8 (VBUS), J2.8 (VBUS), J4.2, R3.2, R4.2, U1.VB, U2.HV
/ADC_L: C3.1, D1.2 (A), D2.1 (K), R9.2, U1.GP40 (GP40/ADC0)
/ADC_R: C5.1, D3.2 (A), D4.1 (K), R12.2, U1.GP41 (GP41/ADC1)
/BIAS_L: C2.1, R7.2, R8.1, R9.1
/BIAS_R: C4.1, R10.2, R11.1, R12.1
/BOOTSEL: SW1.1, U1.BS
/ENC_A: SW3.A, U1.GP4
/ENC_B: SW3.B, U1.GP5
/ENC_PUSH: SW3.S1, U1.GP8
/GND: C1.2, C3.2, C5.2, D2.2 (A), D4.2 (A), D5.1 (K), J1.1 (GND), J2.1 (GND), J3.S, J4.1, R1.2, R2.2, R8.2, R11.2, SW1.2, SW2.2, SW3.C, SW3.S2, U1.GND1 (GND), U1.GND2 (GND), U1.GND3 (GND), U1.GND4 (GND), U1.GND5 (GND), U1.GND6 (GND), U2.GND_H, U2.GND_L
/HOST_GP0_DP: R5.1, U1.GP0
/HOST_GP1_DM: R6.1, U1.GP1
/J1_CC1: J1.7 (CC1), R1.1
/J1_CC2: J1.2 (CC2), R2.1
/J2_CC1: J2.7 (CC1), R3.1
/J2_CC2: J2.2 (CC2), R4.1
/KBD_DM: J2.4 (D-), R6.2
/KBD_DP: J2.5 (D+), R5.2
/LINE_L: C2.2, J3.T
/LINE_R: C4.2, J3.R
/RUN: SW2.1, U1.RUN
/SCL_3V3: U1.GP3, U2.LV2
/SCL_5V: J4.4, U2.HV2
/SDA_3V3: U1.GP2, U2.LV1
/SDA_5V: J4.3, U2.HV1
/STATUS_LED_A: D5.2 (A), R13.2
/STATUS_LED_GP6: R13.1, U1.GP6
/USB_DM: J1.4 (D-), U1.U-
/USB_DP: J1.5 (D+), U1.U+

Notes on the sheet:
PGA2350 CARRIER — ELECTRICAL DRAFT / NOT FOR MANUFACTURE
UPSTREAM: HUB / MAC
MOONLANDER ONLY / ALWAYS-POWERED 5V
STEREO AUDIO — GP40 / GP41
Left
Right
USB HOST SERIES / BULK
BOOT / RESET
DISPLAY LEVEL CONVERSION
ENCODER
STATUS LED / GP6
Module pads use signal names; see separate 90 x 75mm placement study. USB breakouts: published 333011 v1.2.0 pin order; confirm delivered revision. No input-ramp switch, USB-C power controller or factory assembly. Source advertises 1.5A; supported setup remains tested Anker data port + brightness 1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
Capacitor positive terminals face BIAS_L / BIAS_R. BAT85S cathode is pin 1 (band). Clamps are not isolation. All grounds common; route keyboard returns away from audio. Routed review draft; independent follow-up pending.

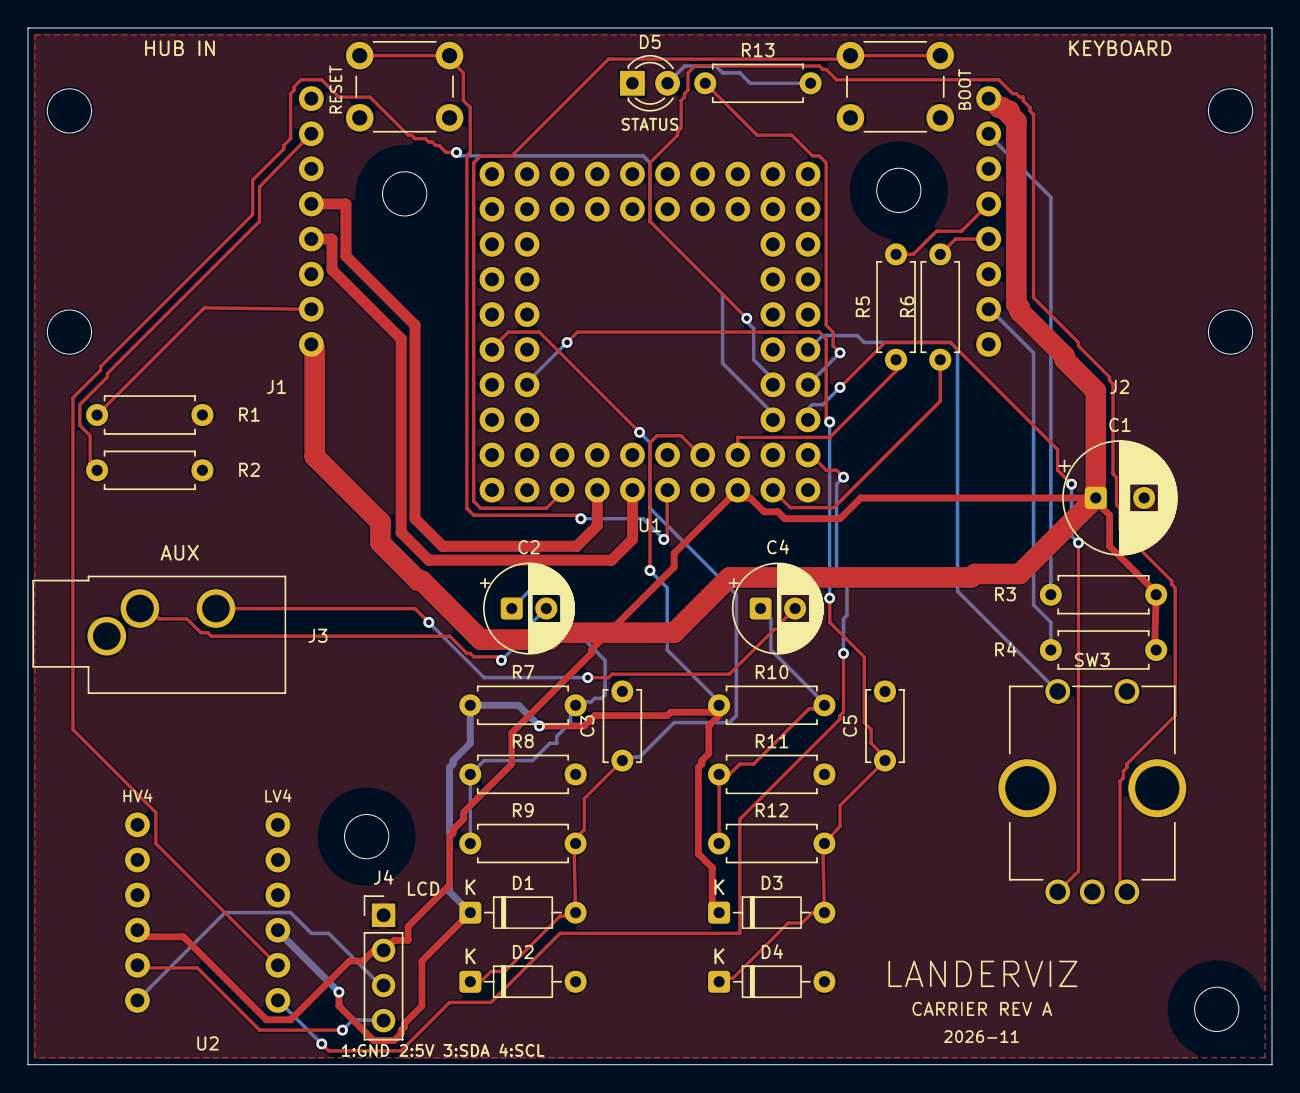
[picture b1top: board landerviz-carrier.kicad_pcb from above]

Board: 2 copper layers, 90.0 x 75.0 mm, 36 parts (0 on the bottom side), 30 nets.

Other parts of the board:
H1, H2, H3, H4: M3 / max OD 7mm; MountingHole_3.2mm_M3_7mmHardware

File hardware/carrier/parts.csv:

references,quantity,unit,item,specification,inventory_status,candidate_mpn,unit_cost_usd,notes
U1,1,module,Pimoroni PGA2350,RP2350B A4 stepping,Purchase pending A4 confirmation,PIM722,11.95,Headers sold separately; previously checked module price; user will ensure A4 before module purchase
J1 J2,2,module,USB-C breakout,Soldered 333011; verify delivered revision,Purchase,333011,2.20,No built-in CC resistors; headers separate; previously checked price
J3,1,jack,Direct right-angle TRS audio jack,Three downward terminals; S ground T left R right,New part requested; purchase pending,SJ1-3533NG,1.69,DigiKey CP1-3533NG-ND; no mating header/socket; not five-pin SJ1-3535NG
U2,1,module,BSS138 level converter,4 channels; 3V3 side and 5V side,Owned; row order user-confirmed 2026-11-07,,,Labelled side HV left LV right; both rows top-down 4 3 GND supply 2 1; 10.16mm row spacing; body approx 12.7x14.3mm
J4,1,header,LCD connection,1x4 male straight 2.54mm pitch,Check owned header kit,,,Use existing female-ended LCD jumper cable
C1,1,capacitor,Bulk electrolytic,470uF >=10V,Owned; user confirms fit 2026-11-07,,,Measured approx 1/4 inch; retain 8mm envelope; 3.5mm lead fit confirmed; lead fit confirmed by user 2026-11-07
C2 C4,2,capacitor,Audio coupling electrolytic,10uF >=16V,Owned; user confirms fit 2026-11-07,,,Measured approx 3/16 inch; reported 50V rating sufficient; retain 6.3mm envelope; 2.5mm lead fit confirmed; lead fit confirmed by user 2026-11-07
C3 C5,2,capacitor,Audio filter ceramic,2.2nF C0G 5% 50V; H5 formed leads at 5mm,Candidate selected; purchase pending,K222J15C0GF5TH5,0.59,DigiKey BC1050CT-ND cut tape; budget higher observed price; body 4.0x2.6mm max fits courtyard; approximate generic fabrication outline; not L2 2.5mm variant
R1 R2,2,resistor,Input CC pull-down,5.1k 1% axial 0.25W,Check owned resistor kit,,,7.62mm lead pitch study
R3 R4 R7 R8 R10 R11,6,resistor,Output CC pull-up and audio bias,22k 1% axial 0.25W,Check owned resistor kit,,,7.62mm lead pitch study
R5 R6,2,resistor,PIO USB series,22 ohm 1% axial 0.25W,Check owned resistor kit,,,7.62mm lead pitch study
R9 R12,2,resistor,Audio series filter,10k 1% axial 0.25W,Check owned resistor kit,,,7.62mm lead pitch study
D1 D2 D3 D4,4,diode,Audio rail clamp,BAT85S axial DO-35,Candidate purchase,BAT85S-TR,0.50,Band marks cathode; DigiKey cut-tape BAT85SCT-ND
SW1 SW2,2,switch,Boot and reset,6mm tactile; 6.5x4.5mm lead-centre pattern,Check inventory or candidate purchase,B3F-1000,0.35,Candidate matches study pattern; schematic still generic switch
SW3,1,encoder,Same Sky rotary encoder with push,12 detents and pulses; 20mm 6mm flat metal shaft; vertical PCB pins,Selected replacement after Astra review; purchase pending,ACZ11BR1E-20FD1-12C,4.33,DigiKey 102-1760-ND; hand solder <=350C <=3s; dedicated ACZ11 footprint; see ENCODER.md; not generic EC11 or Bourns interchangeable
R13,1,resistor,Status LED current limiting,1k 1% axial 0.25W,Check owned resistor kit,,,7.62mm lead pitch; driven from GP6
D5,1,LED,Green status indicator,3mm through-hole; 2.54mm lead pitch,Authorized addition; purchase pending,WP710A10LZGCK,0.59,Pad 1 cathode to GND; pad 2 anode to R13; firmware port pending
PGA_MALE,64,contact,PGA module male pins,2.54mm pitch; socket-mating length to confirm,Check owned header kit,,,Contact count not packaged strip quantity
PGA_SOCKET,64,contact,Carrier PGA female sockets,2.54mm pitch; two 2x10 plus two 2x6 pieces,Owned; small-piece corner paper fit confirmed; long-strip match and cutting pending,,,One 2x40 can supply 32 kept columns plus four discarded cut columns; see socket-frame.svg; second strip stays intact; module mating depth not yet checked; published dimensions/paper fit accepted for ordering by user; full-frame/mating are assembly steps
USB_MALE,16,contact,USB breakout male pins,2.54mm pitch; 8 per module,Check owned header kit,,,Do not duplicate if delivered with suitable pins
USB_SOCKET,16,contact,Carrier USB breakout female sockets,1x8 per module; 2.54mm pitch,Check owned header kit,,,Height and support hardware pending
LEVEL_SOCKET,12,contact,Carrier level converter sockets,2x 1x6; 2.54mm pitch; 10.16mm between rows,Check owned header kit,,,Row spacing from E/G breadboard fit; body orientation and existing male pins to confirm

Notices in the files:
hardware/landerviz.kicad_pcb:
2026-11  /  © 2026 Jon Carl
